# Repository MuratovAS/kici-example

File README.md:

# kici-example

This repository is an example of [kici](https://github.com/MuratovAS/kici) usage, and new features are also tested here.

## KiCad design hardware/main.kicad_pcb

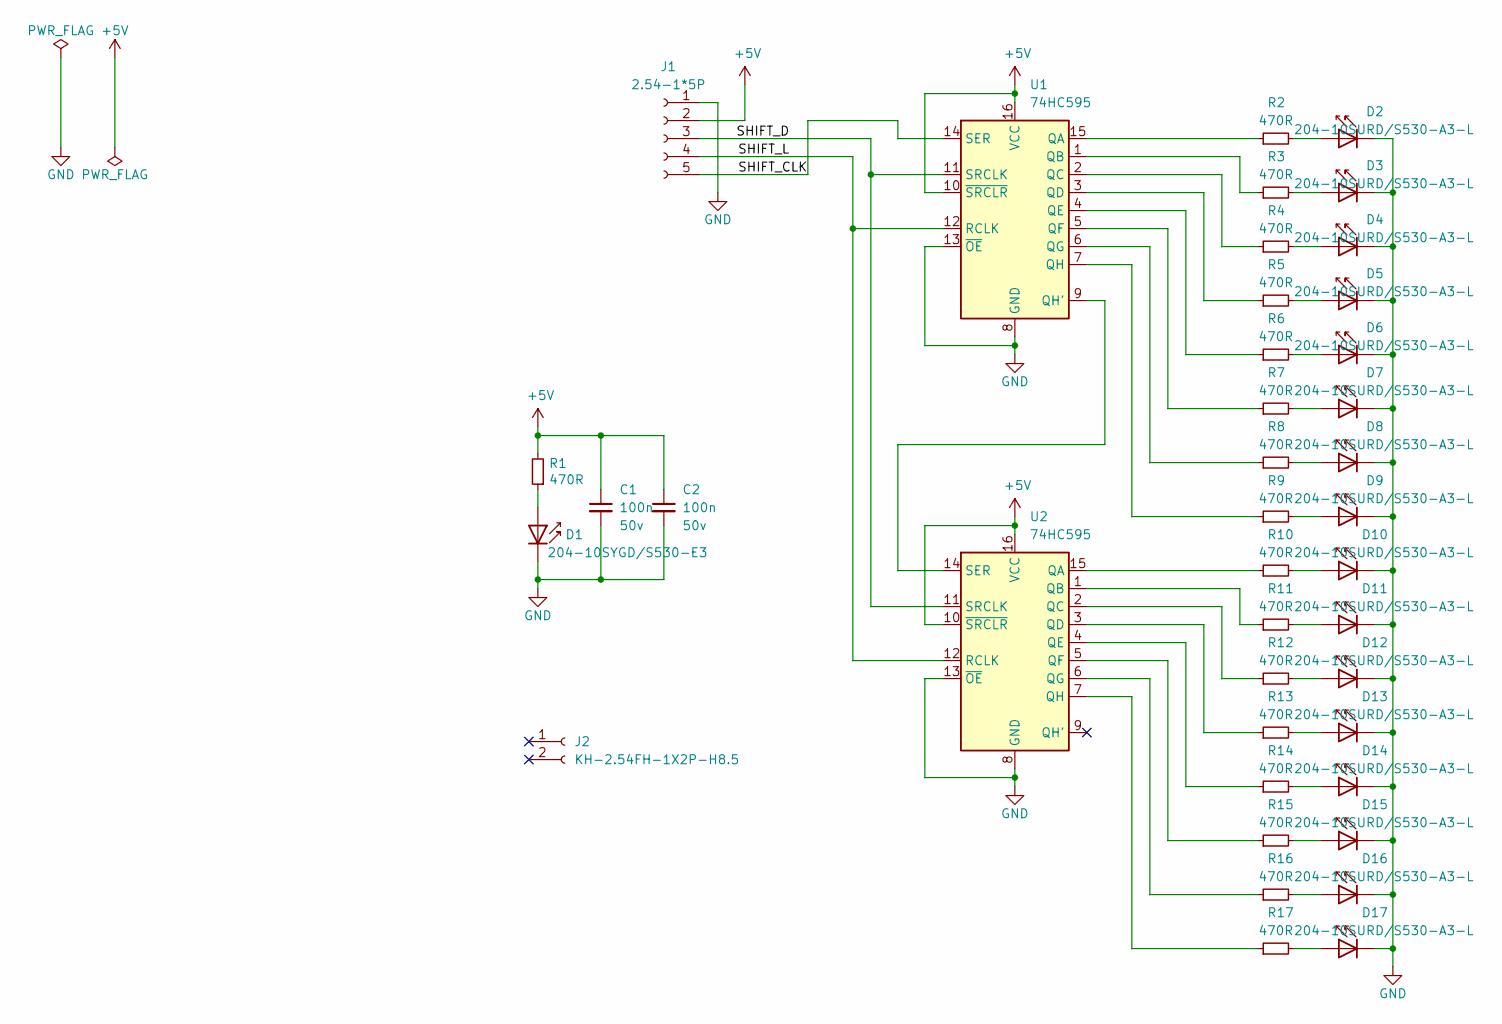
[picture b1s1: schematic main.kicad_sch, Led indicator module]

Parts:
C1, C2: 100n; C_0805_2012Metric; Voltage 50v; lcsc C49678
D1: 204-10SYGD/S530-E3; LED_D3.0mm; lcsc C85161
D2, D3, D4, D5, D6, D7, D8, D9, D10, D11, D12, D13, D14, D15, D16, D17: 204-10SURD/S530-A3-L; LED_D3.0mm; lcsc C99772
J1: 2.54-1*5P; PinSocket_1x05_P2.54mm_Vertical; lcsc C50950
J2: KH-2.54FH-1X2P-H8.5; PinSocket_1x02_P2.54mm_Vertical; lcsc C2905414
R1, R2, R3, R4, R5, R6, R7, R8, R9, R10, R11, R12, R13, R14, R15, R16, R17: 470R; R_0805_2012Metric; lcsc C17710
U1, U2: 74HC595; SOIC-16_3.9x9.9mm_P1.27mm; lcsc C5947

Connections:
+5V: C1.1, C2.1, J1.2, R1.2, U1.10 (~SRCLR), U1.16 (VCC), U2.10 (~SRCLR), U2.16 (VCC)
/SHIFT_CLK: J1.5, U1.14 (SER)
/SHIFT_D: J1.3, U1.11 (SRCLK), U2.11 (SRCLK)
/SHIFT_L: J1.4, U1.12 (RCLK), U2.12 (RCLK)
GND: C1.2, C2.2, D1.1 (K), D2.1 (K), D3.1 (K), D4.1 (K), D5.1 (K), D6.1 (K), D7.1 (K), D8.1 (K), D9.1 (K), D10.1 (K), D11.1 (K), D12.1 (K), D13.1 (K), D14.1 (K), D15.1 (K), D16.1 (K), D17.1 (K), J1.1, U1.8 (GND), U1.13 (~OE), U2.8 (GND), U2.13 (~OE)
unnamed: D1.2 (A), R1.1
unnamed: D2.2 (A), R2.2
unnamed: D3.2 (A), R3.2
unnamed: D4.2 (A), R4.2
unnamed: D5.2 (A), R5.2
unnamed: D6.2 (A), R6.2
unnamed: D7.2 (A), R7.2
unnamed: D8.2 (A), R8.2
unnamed: D9.2 (A), R9.2
unnamed: D10.2 (A), R10.2
unnamed: D11.2 (A), R11.2
unnamed: D12.2 (A), R12.2
unnamed: D13.2 (A), R13.2
unnamed: D14.2 (A), R14.2
unnamed: D15.2 (A), R15.2
unnamed: D16.2 (A), R16.2
unnamed: D17.2 (A), R17.2
unnamed: R2.1, U1.15 (QA)
unnamed: R3.1, U1.1 (QB)
unnamed: R4.1, U1.2 (QC)
unnamed: R5.1, U1.3 (QD)
unnamed: R6.1, U1.4 (QE)
unnamed: R7.1, U1.5 (QF)
unnamed: R8.1, U1.6 (QG)
unnamed: U1.9 (QH'), U2.14 (SER)
unnamed: R9.1, U1.7 (QH)
unnamed: R10.1, U2.15 (QA)
unnamed: R11.1, U2.1 (QB)
unnamed: R12.1, U2.2 (QC)
unnamed: R13.1, U2.3 (QD)
unnamed: R14.1, U2.4 (QE)
unnamed: R15.1, U2.5 (QF)
unnamed: R16.1, U2.6 (QG)
unnamed: R17.1, U2.7 (QH)

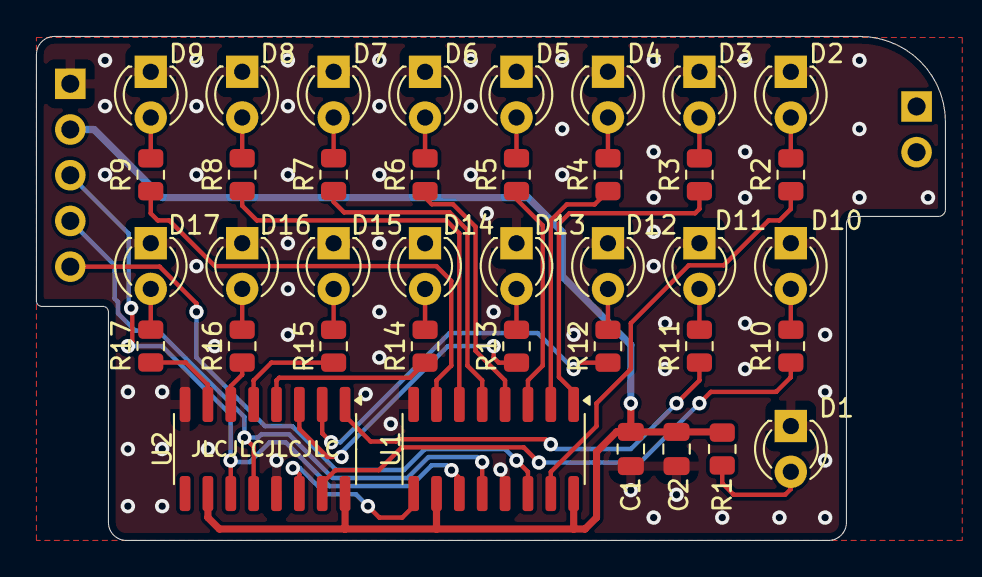
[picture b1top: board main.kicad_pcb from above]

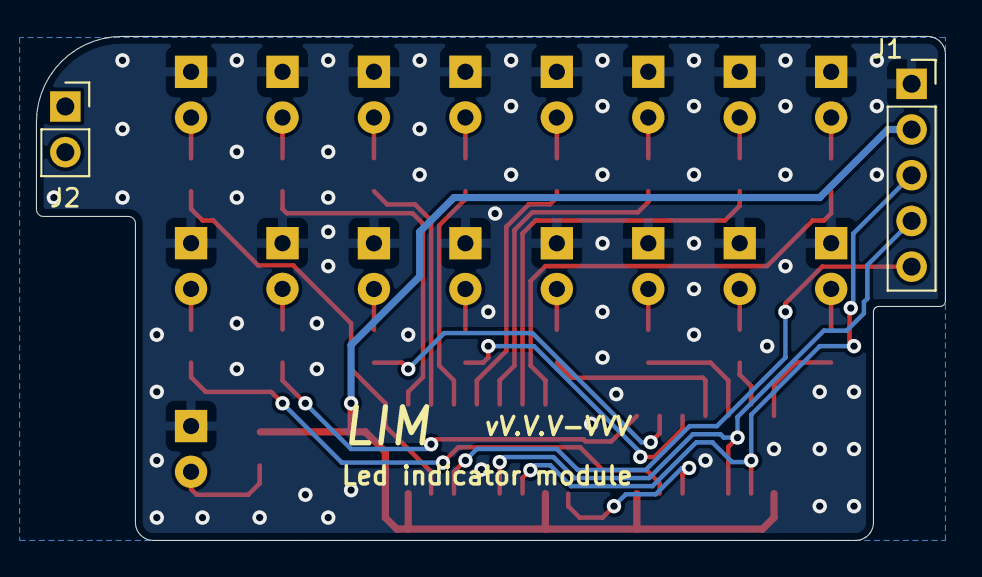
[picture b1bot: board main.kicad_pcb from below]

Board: 2 copper layers, 50.5 x 28.0 mm, 40 parts (2 on the bottom side), 39 nets.

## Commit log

2025-04-19 init
2025-04-19 fix env
2025-04-19 fix ci
2025-04-19 Updating from #1
2025-04-19 destroy the scheme
2025-04-19 destroy pcb; fix sch
2025-04-19 fix pcb
2025-04-19 update zone
2025-04-19 fix space
2025-04-19 fix tabs
2025-04-20 update ci
2025-04-20 Updating from #kici-example_stock_14560568212
2025-04-23 add gitea support
2025-04-29 test erc
2025-04-29 fix erc
